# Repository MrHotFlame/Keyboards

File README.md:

# SwagSplit
My very own split keyboard.

Specs:
- RJ9 Interconnect cable
- Direct wire, no diodes
- Marble Pico MCU

# Swag44
My own Planck like ortholinear keyboard.

Specs:
- RP2040 Zero MCU
- Handwired
- Split spacebar

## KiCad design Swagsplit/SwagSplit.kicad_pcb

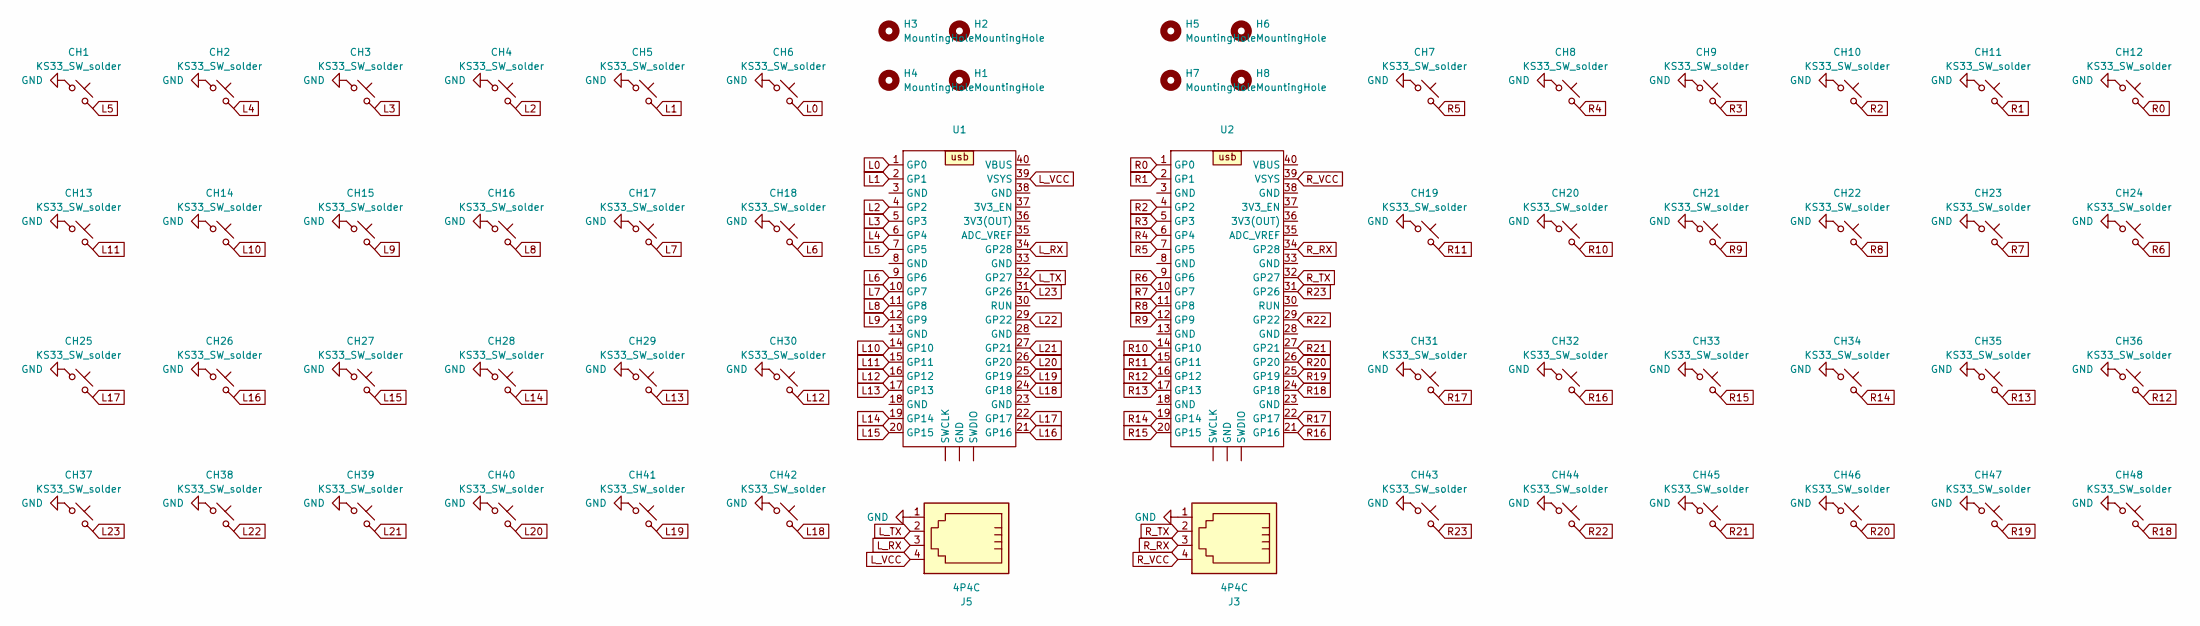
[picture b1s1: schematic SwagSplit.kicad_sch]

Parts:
CH1, CH2, CH3, CH4, CH5, CH6, CH7, CH8, CH9, CH10, CH11, CH12, CH13, CH14, CH15, CH16, CH17, CH18, CH19, CH20, CH21, CH22, CH23, CH24, CH25, CH26, CH27, CH28, CH29, CH30, CH31, CH32, CH33, CH34, CH35, CH36, CH37, CH38, CH39, CH40, CH41, CH42, CH43, CH44, CH45, CH46, CH47, CH48: KS33_SW_solder; SW_Gateron_LowProfile_THT
H1, H2, H3, H4, H5, H6, H7, H8: MountingHole; MountingHole_2.1mm
J3, J5: 4P4C; RJ9_Evercom_5301-440xxx_Horizontal
U1, U2: Raspberry_pi_pico

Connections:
GND: CH1.1, CH2.1, CH3.1, CH4.1, CH5.1, CH6.1, CH7.1, CH8.1, CH9.1, CH10.1, CH11.1, CH12.1, CH13.1, CH14.1, CH15.1, CH16.1, CH17.1, CH18.1, CH19.1, CH20.1, CH21.1, CH22.1, CH23.1, CH24.1, CH25.1, CH26.1, CH27.1, CH28.1, CH29.1, CH30.1, CH31.1, CH32.1, CH33.1, CH34.1, CH35.1, CH36.1, CH37.1, CH38.1, CH39.1, CH40.1, CH41.1, CH42.1, CH43.1, CH44.1, CH45.1, CH46.1, CH47.1, CH48.1, J3.1, J5.1
L0: CH6.2, U1.1 (GP0)
L1: CH5.2, U1.2 (GP1)
L2: CH4.2, U1.4 (GP2)
L3: CH3.2, U1.5 (GP3)
L4: CH2.2, U1.6 (GP4)
L5: CH1.2, U1.7 (GP5)
L6: CH18.2, U1.9 (GP6)
L7: CH17.2, U1.10 (GP7)
L8: CH16.2, U1.11 (GP8)
L9: CH15.2, U1.12 (GP9)
L10: CH14.2, U1.14 (GP10)
L11: CH13.2, U1.15 (GP11)
L12: CH30.2, U1.16 (GP12)
L13: CH29.2, U1.17 (GP13)
L14: CH28.2, U1.19 (GP14)
L15: CH27.2, U1.20 (GP15)
L16: CH26.2, U1.21 (GP16)
L17: CH25.2, U1.22 (GP17)
L18: CH42.2, U1.24 (GP18)
L19: CH41.2, U1.25 (GP19)
L20: CH40.2, U1.26 (GP20)
L21: CH39.2, U1.27 (GP21)
L22: CH38.2, U1.29 (GP22)
L23: CH37.2, U1.31 (GP26)
L_RX: J5.3, U1.34 (GP28)
L_TX: J5.2, U1.32 (GP27)
L_VCC: J5.4, U1.39 (VSYS)
R0: CH12.2, U2.1 (GP0)
R1: CH11.2, U2.2 (GP1)
R2: CH10.2, U2.4 (GP2)
R3: CH9.2, U2.5 (GP3)
R4: CH8.2, U2.6 (GP4)
R5: CH7.2, U2.7 (GP5)
R6: CH24.2, U2.9 (GP6)
R7: CH23.2, U2.10 (GP7)
R8: CH22.2, U2.11 (GP8)
R9: CH21.2, U2.12 (GP9)
R10: CH20.2, U2.14 (GP10)
R11: CH19.2, U2.15 (GP11)
R12: CH36.2, U2.16 (GP12)
R13: CH35.2, U2.17 (GP13)
R14: CH34.2, U2.19 (GP14)
R15: CH33.2, U2.20 (GP15)
R16: CH32.2, U2.21 (GP16)
R17: CH31.2, U2.22 (GP17)
R18: CH48.2, U2.24 (GP18)
R19: CH47.2, U2.25 (GP19)
R20: CH46.2, U2.26 (GP20)
R21: CH45.2, U2.27 (GP21)
R22: CH44.2, U2.29 (GP22)
R23: CH43.2, U2.31 (GP26)
R_RX: J3.3, U2.34 (GP28)
R_TX: J3.2, U2.32 (GP27)
R_VCC: J3.4, U2.39 (VSYS)

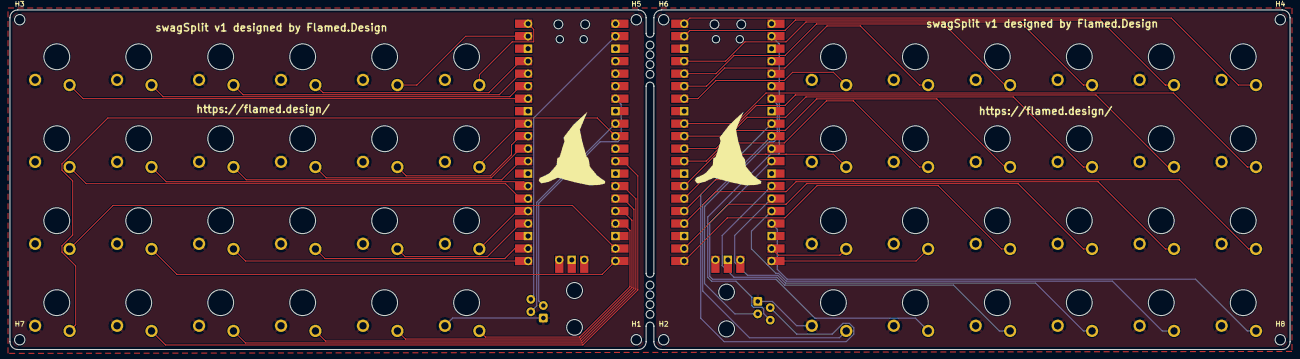
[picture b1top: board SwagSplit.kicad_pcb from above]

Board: 2 copper layers, 260.4 x 69.1 mm, 60 parts (0 on the bottom side), 55 nets.

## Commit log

2025-02-09 KiCAD
2025-02-09 PCB screenshot
2025-02-24 reorganized
2025-02-24 image added
2025-02-24 added CAD files
